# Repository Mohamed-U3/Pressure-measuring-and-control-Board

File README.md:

# ESP‑12 Pressure Control Circuit

A modular ESP‑12E (ESP8266) hardware design for pressure sensing, load driving, and safe power management with battery charging and automatic source switchover.

<div align="center">
  
</div>

<div align="center">
  
</div>

## Overview

This repository contains KiCad 9.0.2 schematics for a pressure‑control system built around an ESP‑12E module, dual precision pressure measurement channels, high‑side battery/adapter power path control, and isolated MOSFET drivers for solenoids and a motor.
The design includes an onboard CN3703 Li‑ion charger, AMS1117‑3.3/LM7805 regulators, TLP250 gate drivers, and IRF540N power MOSFETs with Schottky flyback protection, organized across four hierarchical sheets.

## Schematic set

- ESP‑12 top‑level: ESP‑12E module, boot/EN/RST conditioning, ESD protection, sensor ADCs, and header breakout.
- MOSFETs: Four opto‑isolated TLP250 driver channels feeding IRF540N MOSFETs for Sol_1…Sol_4 and Motor outputs with MBR745 freewheel diodes and LED indicators.
- Automatic Load Switchover: LTC2952 power management, dual 2SJ174 P‑MOSFET path control, and local 3.3 V/5 V regulation for state control and status.
- Battery Charger: CN3703 Li‑ion charger with SS36 rectifiers, 22 µH power inductors, 0.1 Ω sense, and charge/done LED indicators.

## Files and structure

- ESP12E.kicad_sch: Top‑level ESP‑12 sheet with sensors, regulators, ESD, UART, and I/O header.
- MOSFETs.kicad_sch: Isolated drivers, MOSFET power stages, connectors for solenoids and motor.
- Automatic Load Switchover.kicad_sch: LTC2952 control, P‑channel power multiplexing, timing/configuration network.
- Battery Charger.kicad_sch: CN3703 charger stage with power path elements and indicators.

## Power architecture

- Input power is provided via a 12 V PWR connector with bulk filtering (e.g., 470 µF/16 V C3) feeding a 5 V LM7805 and a 3.3 V AMS1117 rail, duplicated where needed on control sheets.
- Automatic source switchover uses LTC2952 to supervise ON/OFF timing, power‑fail, watchdog, and gate‑drive outputs for back‑to‑back 2SJ174 P‑MOSFETs controlling PWR_in/PWR_out and Battery_in.
- The CN3703 charger implements Li‑ion charging with SS36 diodes, 22 µH inductors, 0.1 Ω current sense, and CHRG/DONE LED status, feeding the battery power domain.

## Sensing and ADC

- Two HX710(A/B) precision ADC channels interface differential pressure sensors labeled MPS‑2108, each with Vo+/Vo−, VCC, and local decoupling.
- Each ADC section provides AVDD/DVDD partitioning, PD_SCK/DOUT digital lines to the ESP‑12E, and VREF/AGND nodes for stable measurement.

## Microcontroller core

- ESP‑12E (ESP8266) module exposes GPIO0–GPIO16, UART TX/RX, SPI, ADC (A0), EN, and RST, with pull networks for proper boot mode and reset behavior.
- ESD protection diodes (CESD5V0D3) are placed on sensitive I/O and rails including UART, reset, and 3.3 V nodes to improve robustness.

## Isolated drivers and loads

- Four TLP250 opto‑gate drivers provide isolation between the ESP‑12 logic domain and the IRF540N power stages, each with dedicated gate resistors and LED activity indicators.
- Outputs are presented on headers as Sol_1, Sol_2, Sol_3, Sol_4, and Motor, each clamped by MBR745 Schottky diodes for inductive flyback protection.

## Connectors

- J4 12v PWR: main DC input for the regulator stages and system rails.
- J6–J10: load connectors labeled Sol_1…Sol_4 and Motor for external actuators.
- J3 UART: UART header with GND and supply pins for programming and debug.
- J1/J2 headers: general I/O and power breakouts, including +3.3 V, +5 V, and ground.

## Pin breakout (IO1 1×16)

| Pin/Net        | Function                                   |
| :--------------- | :------------------------------------------- |
| +3.3V          | 3.3 V rail for peripherals                 |
| GND            | Ground reference                           |
| D0/GPIO16      | Wake/deep‑sleep capable digital I/O       |
| D1/SCL/GPIO5   | I2C SCL or GPIO                            |
| D2/SDA/GPIO4   | I2C SDA or GPIO                            |
| D3/GPIO0       | Boot strap/GPIO, used for programming mode |
| D4/GPIO2       | Boot strap/GPIO                            |
| D5/GPIO14/SCLK | SPI SCLK or GPIO                           |
| D6/GPIO12/MISO | SPI MISO or GPIO                           |
| D7/GPIO13/MOSI | SPI MOSI or GPIO                           |
| D8/GPIO15/SS   | Boot strap/SPI SS                          |
| TX/GPIO1       | UART TXD                                   |
| RX/GPIO3       | UART RXD                                   |
| A0/ADC         | Analog input to ESP8266                    |
| GND            | Ground reference                           |

## Boot and programming

- EN and RST are broken out with push‑buttons and pull resistors for stable power‑up and manual reset.
- Boot straps on GPIO0/GPIO2/GPIO15 are provisioned via resistor networks to ensure normal boot, with access for entering programming mode via GPIO0.

## Protections and indicators

- Transient suppression uses CESD5V0D3 devices on supply and data lines close to connectors and the ESP‑12E pins.
- Multiple LEDs indicate power presence, driver activity, and charger state (CHRG/DONE), aiding bring‑up and troubleshooting.

## Build notes

- Designed with KiCad E.D.A. 9.0.2; open the top‑level ESP12E.kicad_sch and traverse hierarchical sheets for editing and ERC.
- Validate regulator thermal performance and inductor/diode current ratings for intended solenoid and motor loads before committing to PCB or enclosure.

## Key components

- MCU and IO: ESP‑12E module with 1×16 IO header and a 1×6 programming/UART header.
- Sensing: 2× HX710(A/B) ADCs with MPS‑2108 pressure sensors and precision analog routing.
- Power: LM7805_TO220, AMS1117‑3.3, bulk/tantalum/ceramic decoupling, and LTC2952‑controlled high‑side switching with 2SJ174 P‑MOSFETs.
- Charger: CN3703 with SS36, 22 µH inductors, 0.1 Ω sense, and charge/done LEDs.
- Drivers: TLP250 opto drivers and IRF540N MOSFETs with MBR745 clamps and LED indicators.

## Getting started

- Power the board from the 12 V input or the battery domain once assembled and verified on bench with dummy loads.
- Program the ESP‑12E via the UART header using normal ESP8266 flashing procedure after pulling GPIO0 low for programming mode.

## Safety

- Observe proper isolation, heat sinking, and wiring gauge for motor/solenoid currents, and verify flyback diodes are oriented correctly before first power‑up.
- Double‑check charger and battery polarity, and do not operate unattended during initial charge‑cycle validation.

## Attribution

Metanoia — designed by Mohamed Yousry, Mechatronics/Embedded Hardware Engineer.

## License

This project is licensed under the [MIT License](LICENSE).

## Version

Schematic Rev v1.0, dated 2025‑09‑07.

## What’s included

- Complete multi‑sheet KiCad schematics with hierarchical organization for core MCU, drivers, switchover, and charging.
- Net labels and headers to speed firmware pin mapping for UART, SPI, I2C, and ADC integration on the ESP‑12E.

## Why this design

The project combines reliable power‑path control, isolated high‑current drivers, and precision sensing into a compact ESP8266 platform for pressure‑based automation tasks.

<div align="center">⁂</div>

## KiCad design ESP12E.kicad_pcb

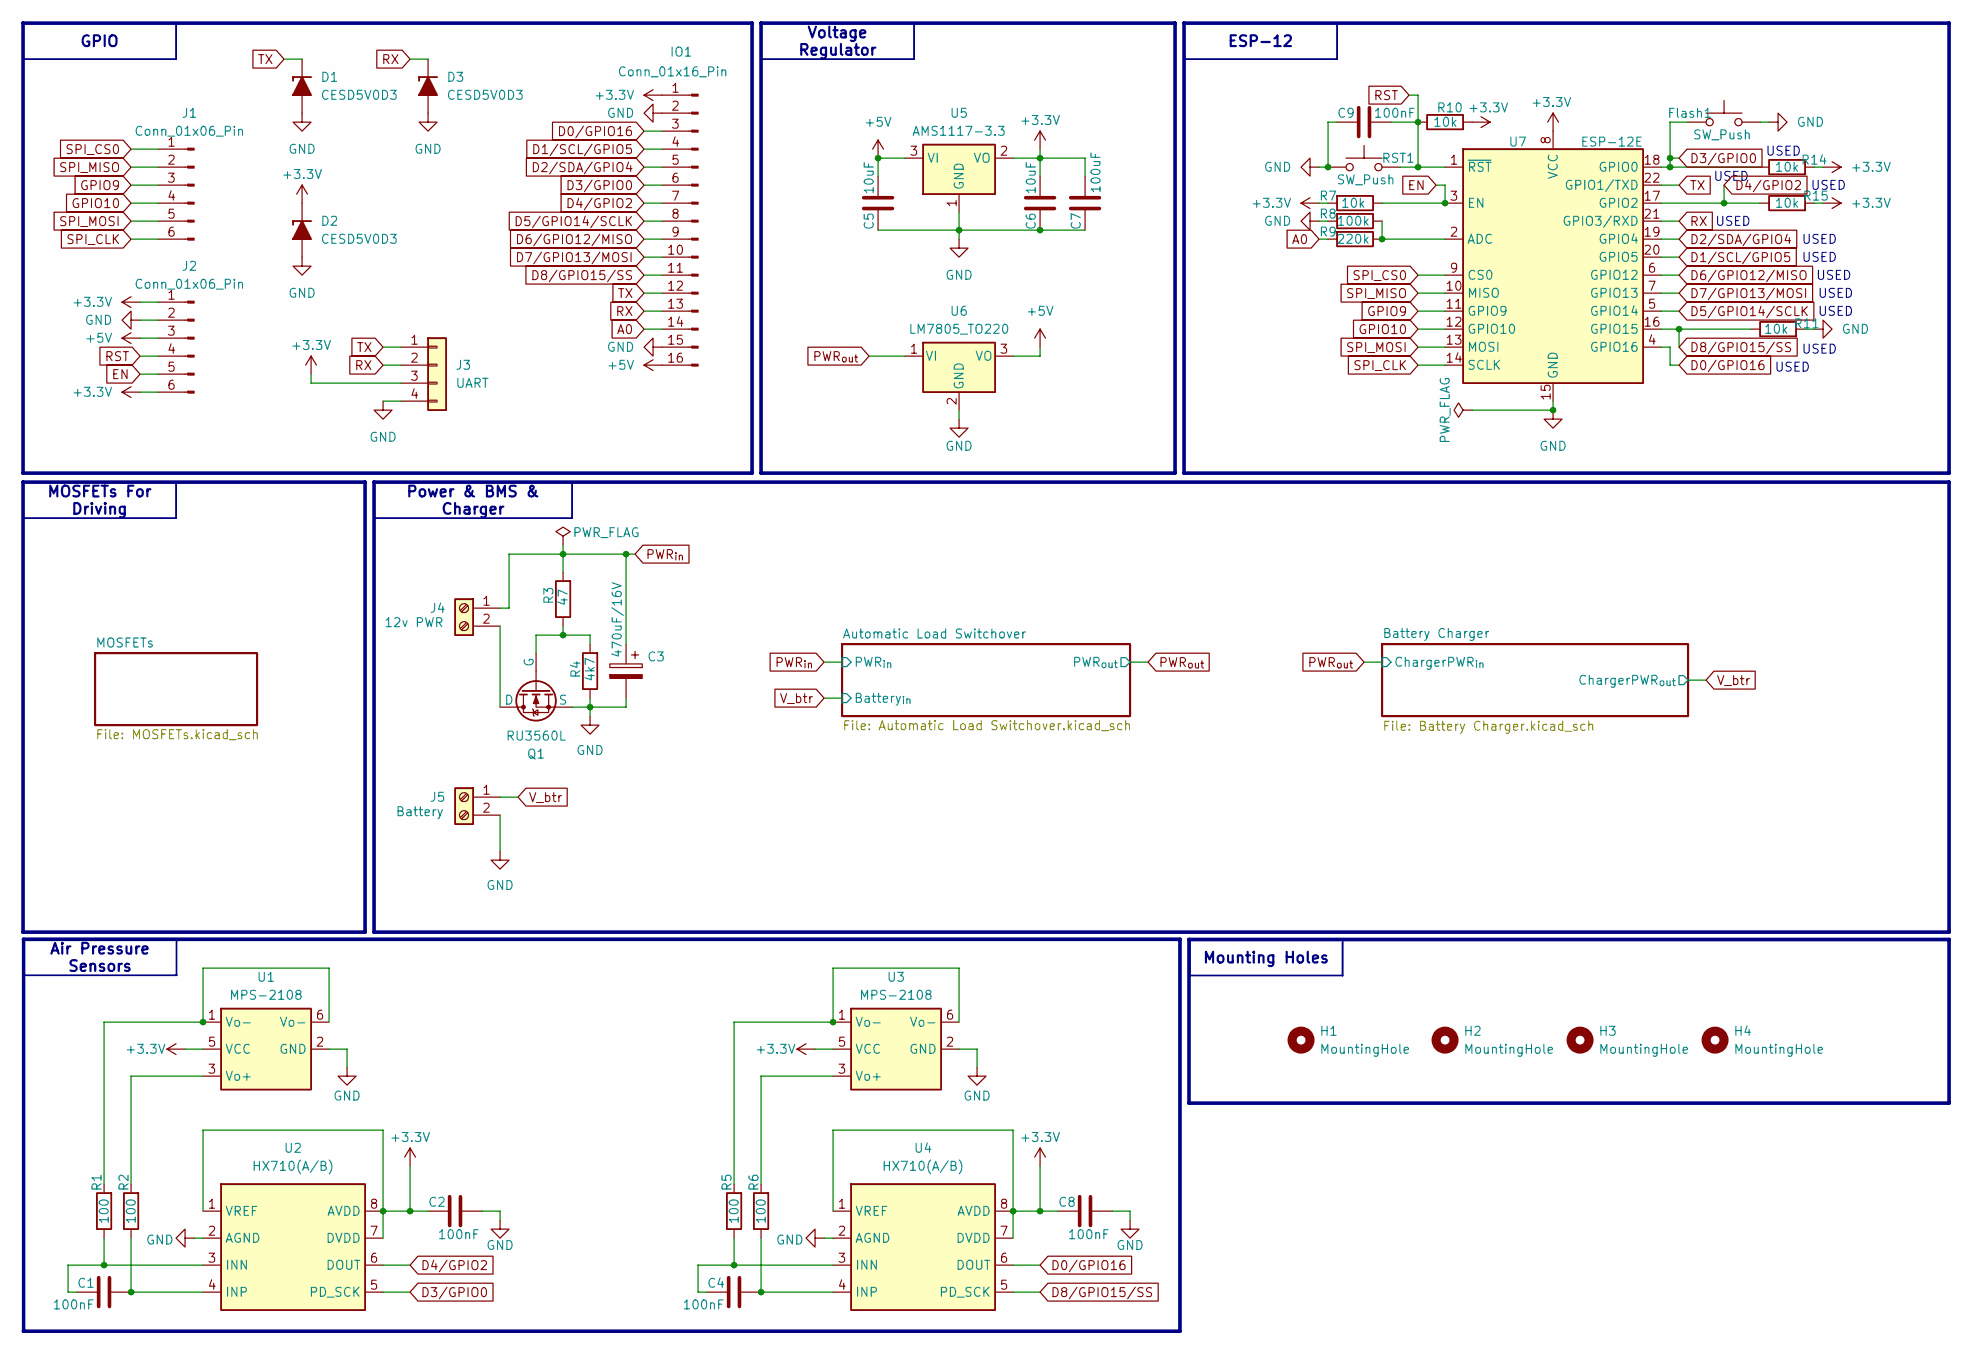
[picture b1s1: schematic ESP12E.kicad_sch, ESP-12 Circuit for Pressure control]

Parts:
C1, C2, C4, C8, C9: 100nF; C_Disc_D3.0mm_W2.0mm_P2.50mm
C3: 470uF/16V; CP_Radial_D10.0mm_P3.80mm
C5, C6: 10uF; C_Radial_D5.0mm_H5.0mm_P2.00mm
C7: 100uF; C_Disc_D3.0mm_W2.0mm_P2.50mm
D1, D2, D3: CESD5V0D3; D_SOD-323_HandSoldering
Flash1: SW_Push; SW_SKRPACE010
H1, H2, H3, H4: MountingHole; MountingHole_2.2mm_M2
IO1: Conn_01x16_Pin; PinHeader_1x16_P2.54mm_Vertical
J1, J2: Conn_01x06_Pin; PinHeader_1x06_P2.54mm_Vertical
J3: UART; JST_XH_B4B-XH-A_1x04_P2.50mm_Vertical
J4: 12v PWR; TerminalBlock_RND_205-00276_1x02_P5.00mm_Vertical
J5: Battery; TerminalBlock_RND_205-00276_1x02_P5.00mm_Vertical
Q1: RU3560L; TO-252-2
R1, R2, R5, R6: 100; R_1206_3216Metric_Pad1.30x1.75mm_HandSolder
R3: 47; R_1206_3216Metric_Pad1.30x1.75mm_HandSolder
R4: 4k7; R_1206_3216Metric_Pad1.30x1.75mm_HandSolder
R7, R10, R11, R14, R15: 10k; R_1206_3216Metric_Pad1.30x1.75mm_HandSolder
R8: 100k; R_1206_3216Metric_Pad1.30x1.75mm_HandSolder
R9: 220k; R_1206_3216Metric_Pad1.30x1.75mm_HandSolder
RST1: SW_Push; SW_SKRPACE010
U1, U3: MPS-2108; DIP-6_W10.16mm
U2, U4: HX710(A/B); SOP-8_3.9x4.9mm_P1.27mm
U5: AMS1117-3.3; SOT-223-3_TabPin2
U6: LM7805_TO220; TO-220-3_Vertical
U7: ESP-12E

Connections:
+3.3V: C2.1, C6.2, C7.2, C8.1, D2.1 (K), IO1.1, J2.1, J2.6, J3.3, R7.2, R10.2, R14.2, R15.2, U1.5 (VCC), U2.1 (VREF), U2.7 (DVDD), U2.8 (AVDD), U3.5 (VCC), U4.1 (VREF), U4.7 (DVDD), U4.8 (AVDD), U5.2 (VO), U7.8 (VCC)
+5V: C5.2, IO1.16, J2.3, U5.3 (VI), U6.3 (VO)
A0: IO1.14, R9.2
D0/GPIO16: IO1.3, U4.6 (DOUT), U7.4 (GPIO16)
D1/SCL/GPIO5: IO1.4, U7.20 (GPIO5); also elsewhere on the board
D2/SDA/GPIO4: IO1.5, U7.19 (GPIO4); also elsewhere on the board
D3/GPIO0: Flash1.2, IO1.6, R14.1, U2.5 (PD_SCK), U7.18 (GPIO0)
D4/GPIO2: IO1.7, R15.1, U2.6 (DOUT), U7.17 (GPIO2)
D5/GPIO14/SCLK: IO1.8, U7.5 (GPIO14); also elsewhere on the board
D6/GPIO12/MISO: IO1.9, U7.6 (GPIO12); also elsewhere on the board
D7/GPIO13/MOSI: IO1.10, U7.7 (GPIO13); also elsewhere on the board
D8/GPIO15/SS: IO1.11, R11.1, U4.5 (PD_SCK), U7.16 (GPIO15)
EN: J2.5, R7.1, U7.3 (EN)
GND: C2.2, C3.2, C5.1, C6.1, C7.1, C8.2, C9.1, D1.2 (A), D2.2 (A), D3.2 (A), Flash1.1, IO1.2, IO1.15, J2.2, J3.4, J5.2, Q1.3 (S), R4.1, R8.2, R11.2, RST1.1, U1.2 (GND), U2.2 (AGND), U3.2 (GND), U4.2 (AGND), U5.1 (GND), U6.2 (GND), U7.15 (GND); also elsewhere on the board
GPIO9: J1.3, U7.11 (GPIO9)
GPIO10: J1.4, U7.12 (GPIO10)
unnamed: J4.2, Q1.2 (D)
unnamed: Q1.1 (G), R3.1, R4.2
unnamed: R1.2, U1.1 (Vo-), U1.6 (Vo-)
unnamed: R5.2, U3.1 (Vo-), U3.6 (Vo-)
unnamed: R2.2, U1.3 (Vo+)
unnamed: C1.1, R1.1, U2.3 (INN)
unnamed: C1.2, R2.1, U2.4 (INP)
unnamed: R6.2, U3.3 (Vo+)
unnamed: C4.1, R5.1, U4.3 (INN)
unnamed: C4.2, R6.1, U4.4 (INP)
unnamed: R8.1, R9.1, U7.2 (ADC)
PWR_{in}: C3.1, J4.1, R3.2; also elsewhere on the board
PWR_{out}: U6.1 (VI); also elsewhere on the board
RST: C9.2, J2.4, R10.1, RST1.2, U7.1 (~RST)
RX: D3.1 (K), IO1.13, J3.2, U7.21 (GPIO3/RXD)
SPI_CLK: J1.6, U7.14 (SCLK)
SPI_CS0: J1.1, U7.9 (CS0)
SPI_MISO: J1.2, U7.10 (MISO)
SPI_MOSI: J1.5, U7.13 (MOSI)
TX: D1.1 (K), IO1.12, J3.1, U7.22 (GPIO1/TXD)
V_btr: J5.1; also elsewhere on the board

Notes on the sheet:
USED
MOSFETs For Driving
ESP-12
Power & BMS & Charger
GPIO
Voltage Regulator
Air Pressure Sensors
Mounting Holes

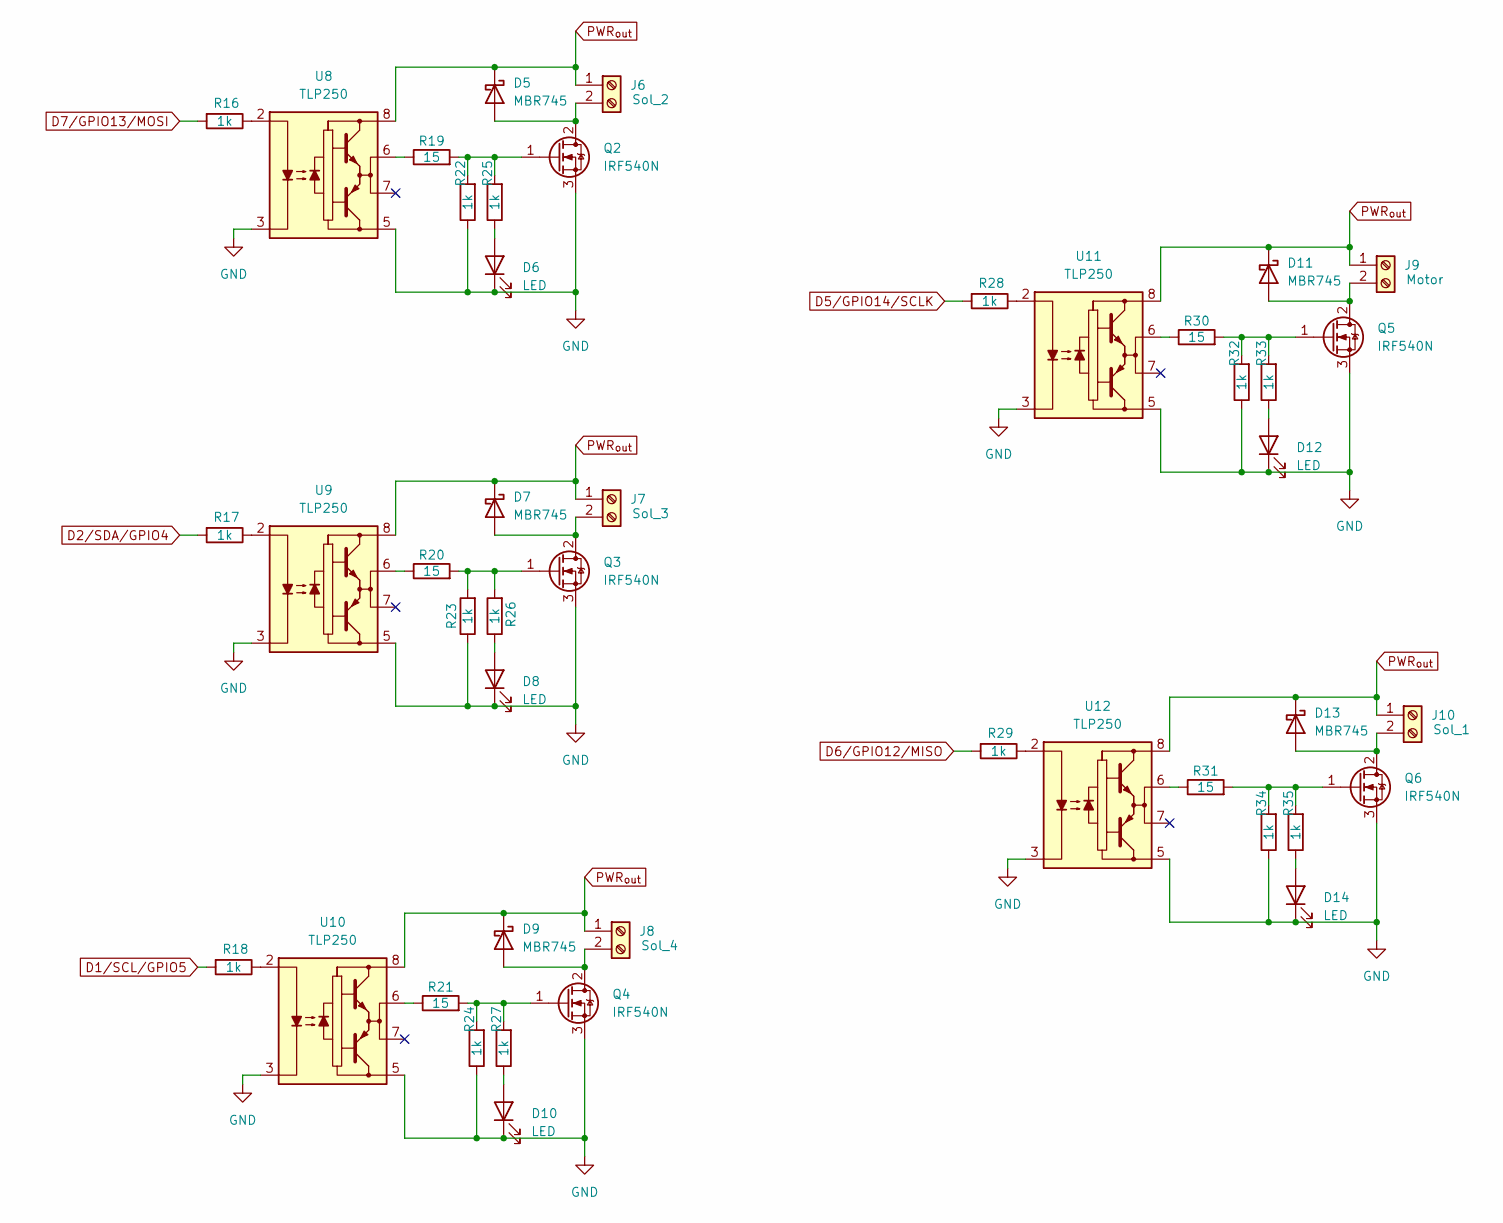
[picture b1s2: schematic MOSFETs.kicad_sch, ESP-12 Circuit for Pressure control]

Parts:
D5, D7, D9, D11, D13: MBR745; TO-220-2_Vertical
D6, D8, D10, D12, D14: LED; LED_1206_3216Metric
J6: Sol_2; TerminalBlock_RND_205-00276_1x02_P5.00mm_Vertical
J7: Sol_3; TerminalBlock_RND_205-00276_1x02_P5.00mm_Vertical
J8: Sol_4; TerminalBlock_RND_205-00276_1x02_P5.00mm_Vertical
J9: Motor; TerminalBlock_RND_205-00276_1x02_P5.00mm_Vertical
J10: Sol_1; TerminalBlock_RND_205-00276_1x02_P5.00mm_Vertical
Q2, Q3, Q4, Q5, Q6: IRF540N; TO-220-3_Vertical
R16, R17, R18, R22, R23, R24, R25, R26, R27, R28, R29, R32, R33, R34, R35: 1k; R_1206_3216Metric_Pad1.30x1.75mm_HandSolder
R19, R20, R21, R30, R31: 15; R_1206_3216Metric_Pad1.30x1.75mm_HandSolder
U8, U9, U10, U11, U12: TLP250; DIP-8_W7.62mm

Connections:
D1/SCL/GPIO5: R18.2; also elsewhere on the board
D2/SDA/GPIO4: R17.2; also elsewhere on the board
D5/GPIO14/SCLK: R28.2; also elsewhere on the board
D6/GPIO12/MISO: R29.2; also elsewhere on the board
D7/GPIO13/MOSI: R16.2; also elsewhere on the board
GND: D6.1 (K), D8.1 (K), D10.1 (K), D12.1 (K), D14.1 (K), Q2.3 (S), Q3.3 (S), Q4.3 (S), Q5.3 (S), Q6.3 (S), R22.1, R23.1, R24.1, R32.1, R34.1, U8.3 (C), U8.5 (VEE), U9.3 (C), U9.5 (VEE), U10.3 (C), U10.5 (VEE), U11.3 (C), U11.5 (VEE), U12.3 (C), U12.5 (VEE); also elsewhere on the board
unnamed: D5.2 (A), J6.2, Q2.2 (D)
unnamed: D6.2 (A), R25.1
unnamed: D7.2 (A), J7.2, Q3.2 (D)
unnamed: D8.2 (A), R26.1
unnamed: D9.2 (A), J8.2, Q4.2 (D)
unnamed: D10.2 (A), R27.1
unnamed: D11.2 (A), J9.2, Q5.2 (D)
unnamed: D12.2 (A), R33.1
unnamed: D13.2 (A), J10.2, Q6.2 (D)
unnamed: D14.2 (A), R35.1
unnamed: Q2.1 (G), R19.2, R22.2, R25.2
unnamed: Q3.1 (G), R20.2, R23.2, R26.2
unnamed: Q4.1 (G), R21.2, R24.2, R27.2
unnamed: Q5.1 (G), R30.2, R32.2, R33.2
unnamed: Q6.1 (G), R31.2, R34.2, R35.2
unnamed: R19.1, U8.6 (VO)
unnamed: R20.1, U9.6 (VO)
unnamed: R21.1, U10.6 (VO)
unnamed: R30.1, U11.6 (VO)
unnamed: R31.1, U12.6 (VO)
unnamed: R16.1, U8.2 (A)
unnamed: R17.1, U9.2 (A)
unnamed: R18.1, U10.2 (A)
unnamed: R28.1, U11.2 (A)
unnamed: R29.1, U12.2 (A)
PWR_{out}: D5.1 (K), D7.1 (K), D9.1 (K), D11.1 (K), D13.1 (K), J6.1, J7.1, J8.1, J9.1, J10.1, U8.8 (VCC), U9.8 (VCC), U10.8 (VCC), U11.8 (VCC), U12.8 (VCC); also elsewhere on the board

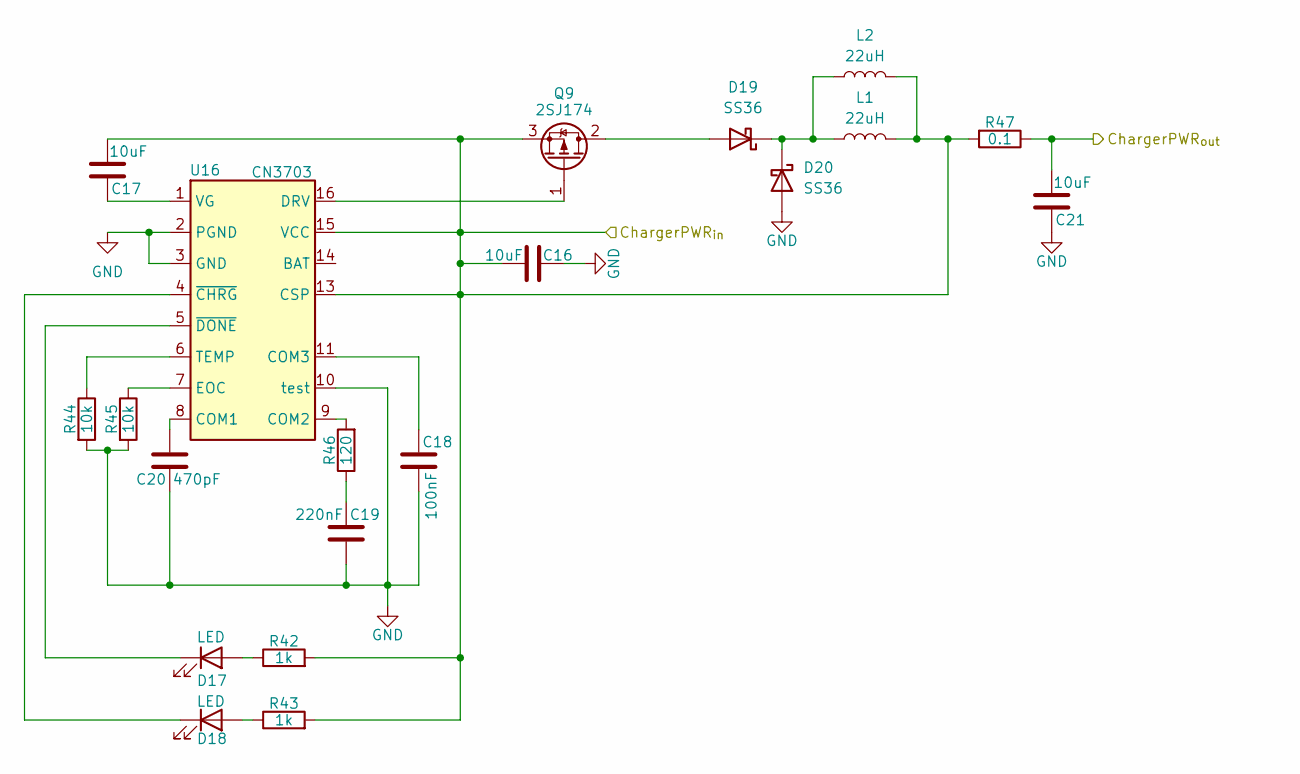
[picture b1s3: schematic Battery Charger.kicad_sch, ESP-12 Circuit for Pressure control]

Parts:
C16, C17, C21: 10uF; C_Radial_D5.0mm_H5.0mm_P2.00mm
C18: 100nF; C_Disc_D3.0mm_W2.0mm_P2.50mm
C19: 220nF; C_Disc_D3.0mm_W2.0mm_P2.50mm
C20: 470pF; C_Disc_D3.0mm_W2.0mm_P2.50mm
D17, D18: LED; LED_1206_3216Metric
D19, D20: SS36; D_SMA
L1, L2: 22uH; L_12x12mm_H4.5mm
Q9: 2SJ174; TO-220-3_Vertical
R42, R43: 1k; R_1206_3216Metric_Pad1.30x1.75mm_HandSolder
R44, R45: 10k; R_1206_3216Metric_Pad1.30x1.75mm_HandSolder
R46: 120; R_1206_3216Metric_Pad1.30x1.75mm_HandSolder
R47: 0.1; R_2512_6332Metric_Pad1.40x3.35mm_HandSolder
U16: CN3703; TSSOP-16_4.4x5mm_P0.65mm

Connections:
GND: C16.1, C18.1, C19.1, C20.1, C21.1, D20.2 (A), R44.2, R45.2, U16.2 (PGND), U16.3 (GND), U16.10 (test); also elsewhere on the board
unnamed: C19.2, R46.1
unnamed: D17.2 (A), R42.1
unnamed: D17.1 (K), U16.5 (~DONE)
unnamed: D18.2 (A), R43.1
unnamed: D18.1 (K), U16.4 (~CHRG)
unnamed: D19.2 (A), Q9.2 (D)
unnamed: D19.1 (K), D20.1 (K), L1.1, L2.1
unnamed: Q9.1 (G), U16.16 (DRV)
unnamed: C20.2, U16.8 (COM1)
unnamed: R46.2, U16.9 (COM2)
unnamed: C18.2, U16.11 (COM3)
unnamed: R45.1, U16.7 (EOC)
unnamed: R44.1, U16.6 (TEMP)
unnamed: C17.1, U16.1 (VG)
PWR_{out}: C16.2, C17.2, L1.2, L2.2, Q9.3 (S), R42.2, R43.2, R47.2, U16.13 (CSP), U16.15 (VCC); also elsewhere on the board
V_btr: C21.2, R47.1; also elsewhere on the board

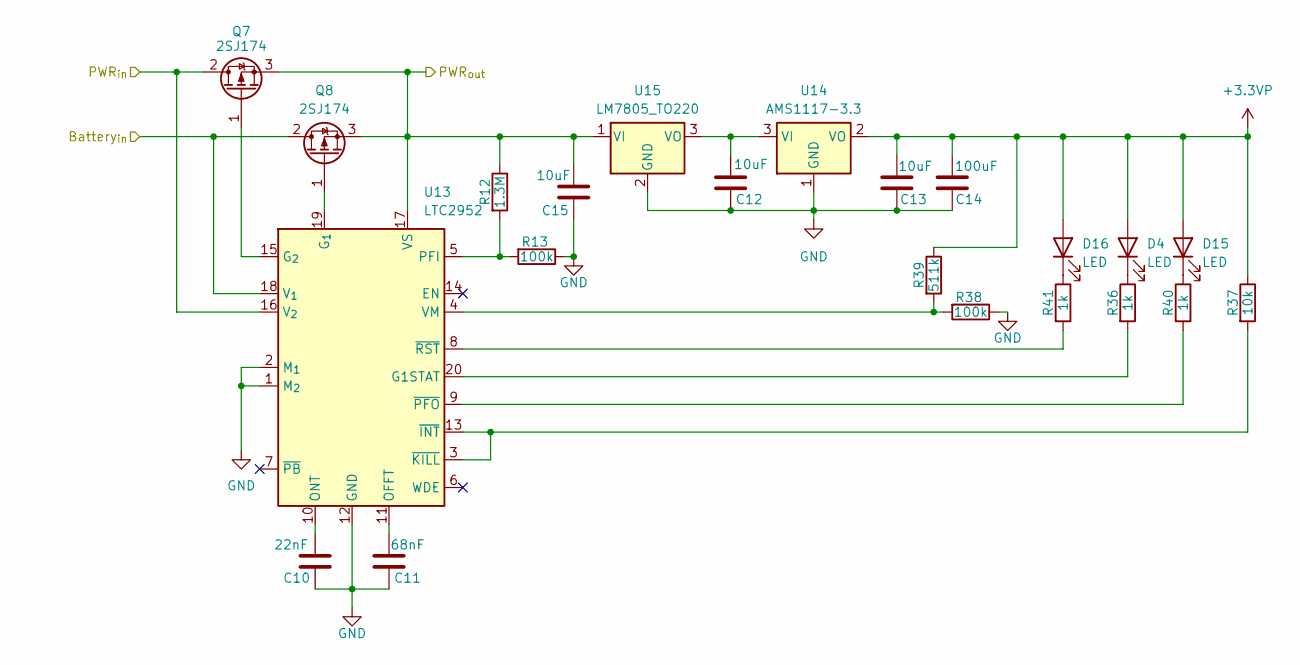
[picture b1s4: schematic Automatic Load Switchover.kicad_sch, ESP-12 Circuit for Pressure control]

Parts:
C10: 22nF; C_Disc_D3.0mm_W2.0mm_P2.50mm
C11: 68nF; C_Disc_D3.0mm_W2.0mm_P2.50mm
C12, C13, C15: 10uF; C_Radial_D5.0mm_H5.0mm_P2.00mm
C14: 100uF; C_Disc_D3.0mm_W2.0mm_P2.50mm
D4, D15, D16: LED; LED_1206_3216Metric
Q7, Q8: 2SJ174; TO-220-3_Vertical
R12: 1.3M; R_1206_3216Metric_Pad1.30x1.75mm_HandSolder
R13, R38: 100k; R_1206_3216Metric_Pad1.30x1.75mm_HandSolder
R36, R40, R41: 1k; R_1206_3216Metric_Pad1.30x1.75mm_HandSolder
R37: 10k; R_1206_3216Metric_Pad1.30x1.75mm_HandSolder
R39: 511k; R_1206_3216Metric_Pad1.30x1.75mm_HandSolder
U13: LTC2952; ETSSOP-20-1EP_4.4x6.5mm_P0.65mm_EP3x4.2mm
U14: AMS1117-3.3; SOT-223-3_TabPin2
U15: LM7805_TO220; TO-220-3_Vertical

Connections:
+3.3VP: C13.2, C14.2, D4.2 (A), D15.2 (A), D16.2 (A), R37.1, R39.1, U14.2 (VO)
GND: C10.1, C11.1, C12.1, C13.1, C14.1, C15.1, R13.1, R38.1, U13.1 (M_{2}), U13.2 (M_{1}), U13.12 (GND), U14.1 (GND), U15.2 (GND); also elsewhere on the board
unnamed: D4.1 (K), R36.1
unnamed: D15.1 (K), R40.1
unnamed: D16.1 (K), R41.1
unnamed: Q7.1 (G), U13.15 (G_{2})
unnamed: Q8.1 (G), U13.19 (G_{1})
unnamed: R36.2, U13.20 (G1STAT)
unnamed: C11.2, U13.11 (OFFT)
unnamed: C10.2, U13.10 (ONT)
unnamed: R12.2, R13.2, U13.5 (PFI)
unnamed: R38.2, R39.2, U13.4 (VM)
unnamed: R37.2, U13.3 (~KILL), U13.13 (~INT)
unnamed: R40.2, U13.9 (~PFO)
unnamed: R41.2, U13.8 (~RST)
unnamed: C12.2, U14.3 (VI), U15.3 (VO)
PWR_{in}: Q7.2 (D), U13.16 (V_{2}); also elsewhere on the board
PWR_{out}: C15.2, Q7.3 (S), Q8.3 (S), R12.1, U13.17 (VS), U15.1 (VI); also elsewhere on the board
V_btr: Q8.2 (D), U13.18 (V_{1}); also elsewhere on the board

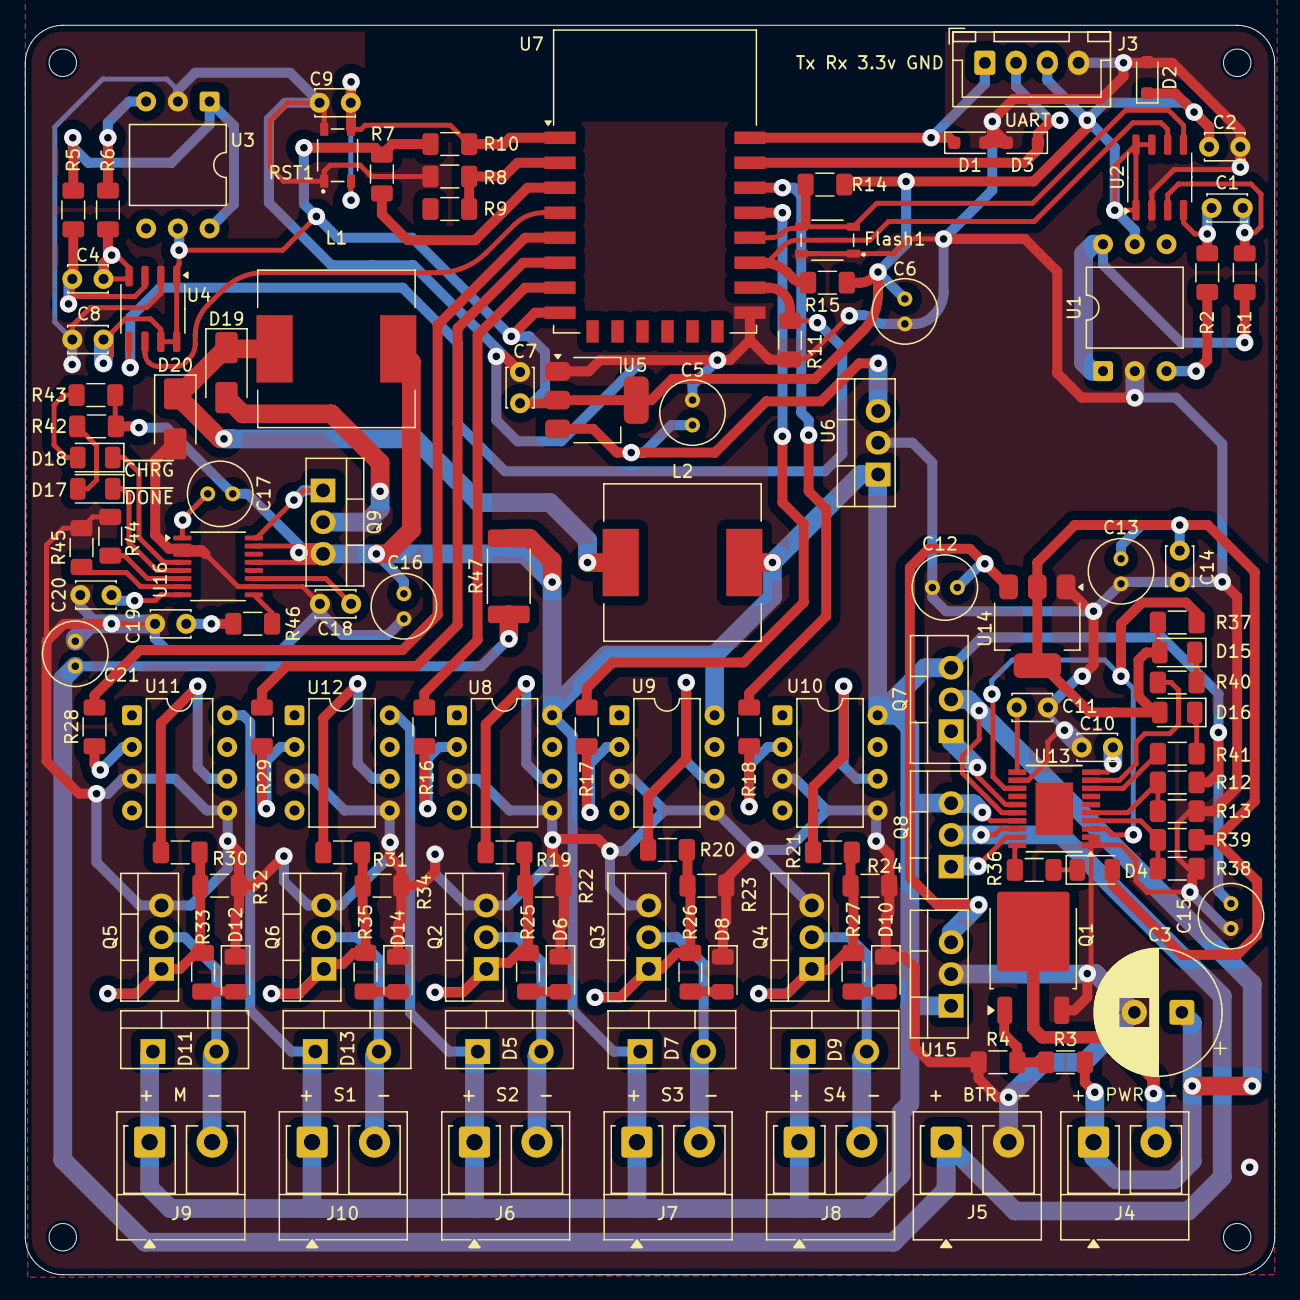
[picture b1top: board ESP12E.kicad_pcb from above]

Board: 2 copper layers, 100.0 x 100.0 mm, 129 parts (0 on the bottom side), 84 nets.

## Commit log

2025-09-07 First commit: this is a template for ESP-12 that is gonna be modified for the requirements.
2025-09-07 Feat: adding IRF520 mosfets for controlling Motor of air pump and 4 solinoids.
2025-09-08 feat: pcb is ok now, next Pressure sensor.
2025-09-09 Working: on adding air pressure sensors (MPS-2108).
2025-09-09 add: Doc files (datasheets).
2025-09-09 feat: the pressure sensor and some protections (flyback diode) is added.
2025-09-10 Feat: adding TLP250 for Isolation and driving MOSFETs.
2025-09-10 working: continue at Work.
2025-09-12 Feat: adding Buck converter + making BOM files HTML with LINKs of stores + small edits + adding polarity protection.
2025-09-12 Fix: edit pcb for manufacturing Bad process (local manufacturing).
2025-09-13 Feat: the board now has a circuit that manage the switch between Battery and Adaptor Power.
2025-09-14 feat: Battery charging Circuit is added.
2025-09-14 doc: README.md file.
2025-09-14 Final: small edit on silkscreen + BOM file + generating Gerber file.
2025-09-14 doc: edit README.md file.
2025-09-18 fix: modification for prefection.
2025-09-18 fix: PCB file was corrupted and unable to open.
2025-09-20 fix: more Via for better soldering on local production PCB.
